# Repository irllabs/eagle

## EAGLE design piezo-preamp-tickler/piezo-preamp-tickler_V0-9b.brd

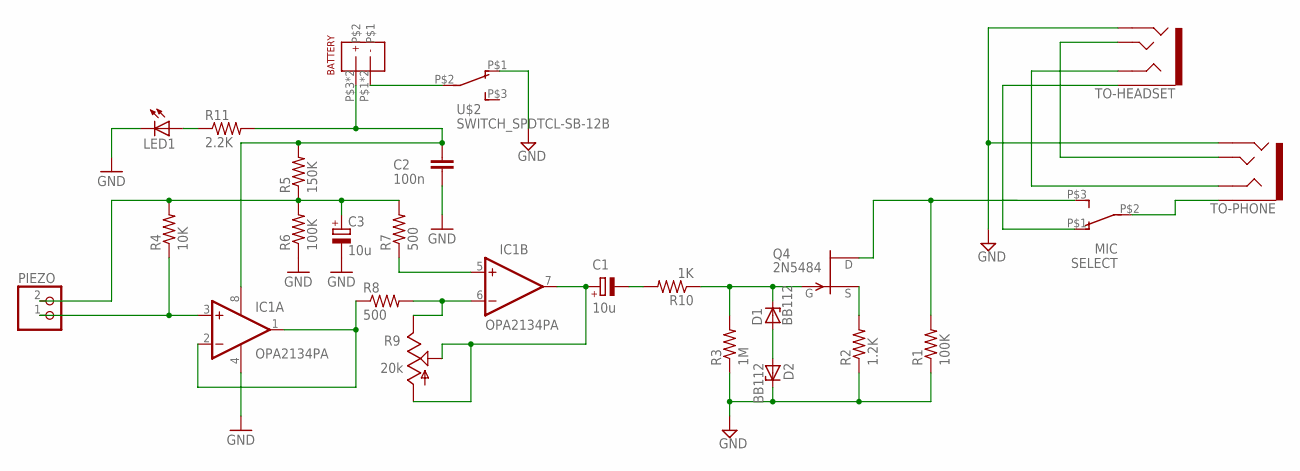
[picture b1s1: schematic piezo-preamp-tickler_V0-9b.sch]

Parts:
BATTERY: BATTERY-A27; BATTERY-A27-KEYSTONE-3651
C1, C3: 10u; TT2D5L
C2: 100n; C025-025X050
D1, D2: BB112; ZDIO-5
IC1: OPA2134PA; DIL08
LED1: LED3MM
PIEZO: JST_2PIN-THM; JST-PH-2-THM
Q4: 2N5484; TO92-
R1, R6: 100K; 0204/7
R2: 1.2K; 0204/7
R3: 1M; 0204/7
R4: 10K; 0204/7
R5: 150K; 0204/7
R7, R8: 500; 0204/7
R9: 20k; TRIMPOT-BOURNS-3306F
R10: 1K; 0204/7
R11: 2.2K; 0204/7
SELECT: MIC; SWITCH_SPDT_CL-SB-12B
TO-HEADSET: AUDIO-JACK3LGPADS; AUDIO-JACK-TRRS-SMD
TO-PHONE: AUDIO-JACK3LGPADS; AUDIO-JACK-TRRS-SMD
U$2: SWITCH_SPDTCL-SB-12B; SWITCH_SPDT_CL-SB-12B

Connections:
GND: C2.1, C3.-, D2.C, IC1.4 (V-), LED1.K (C), R1.1, R2.1, R3.1, R6.1, TO-HEADSET.RING2, TO-PHONE.RING2, U$2.P$1 (1)
unnamed: D1.A, D2.A
unnamed: BATTERY.P$1, BATTERY.P$2, U$2.P$2 (2)
unnamed: Q4.2 (S), R2.2
unnamed: IC1.5 (+IN), R7.1
unnamed: C1.+, IC1.7 (OUT), R9.P$1 (IN), R9.P$2 (WIPER)
unnamed: IC1.6 (-IN), R8.2, R9.P$3 (OUT)
unnamed: C3.+, PIEZO.2 (1), R4.2, R5.1, R6.2, R7.2
unnamed: IC1.3 (+IN), PIEZO.1 (2), R4.1
unnamed: D1.C, Q4.1 (G), R3.2, R10.1
unnamed: C1.-, R10.2
unnamed: SELECT.P$1 (1), TO-HEADSET.EARTH
unnamed: TO-HEADSET.TIP, TO-PHONE.TIP
unnamed: IC1.1 (OUT), IC1.2 (-IN), R8.1
unnamed: TO-HEADSET.RING1, TO-PHONE.RING1
unnamed: LED1.A, R11.1
unnamed: SELECT.P$2 (2), TO-PHONE.EARTH
SELECT: Q4.3 (D), R1.2, SELECT.P$3 (3)
V9V: BATTERY.P$3, BATTERY.P$4, C2.2, IC1.8 (V+), R5.2, R11.2

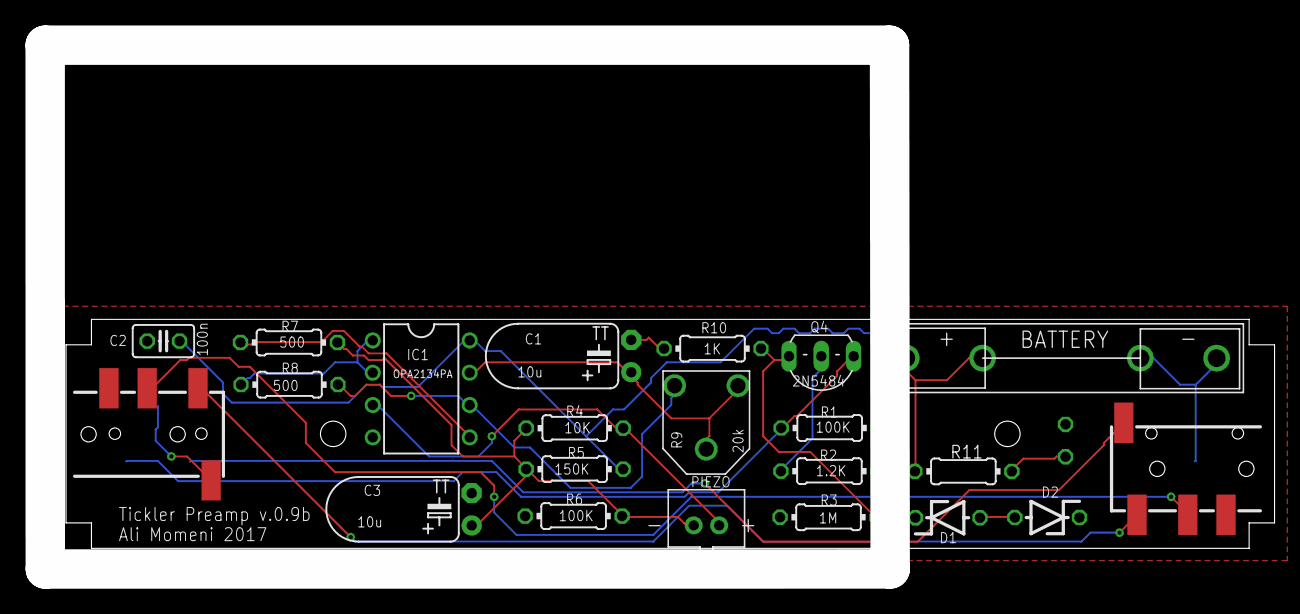
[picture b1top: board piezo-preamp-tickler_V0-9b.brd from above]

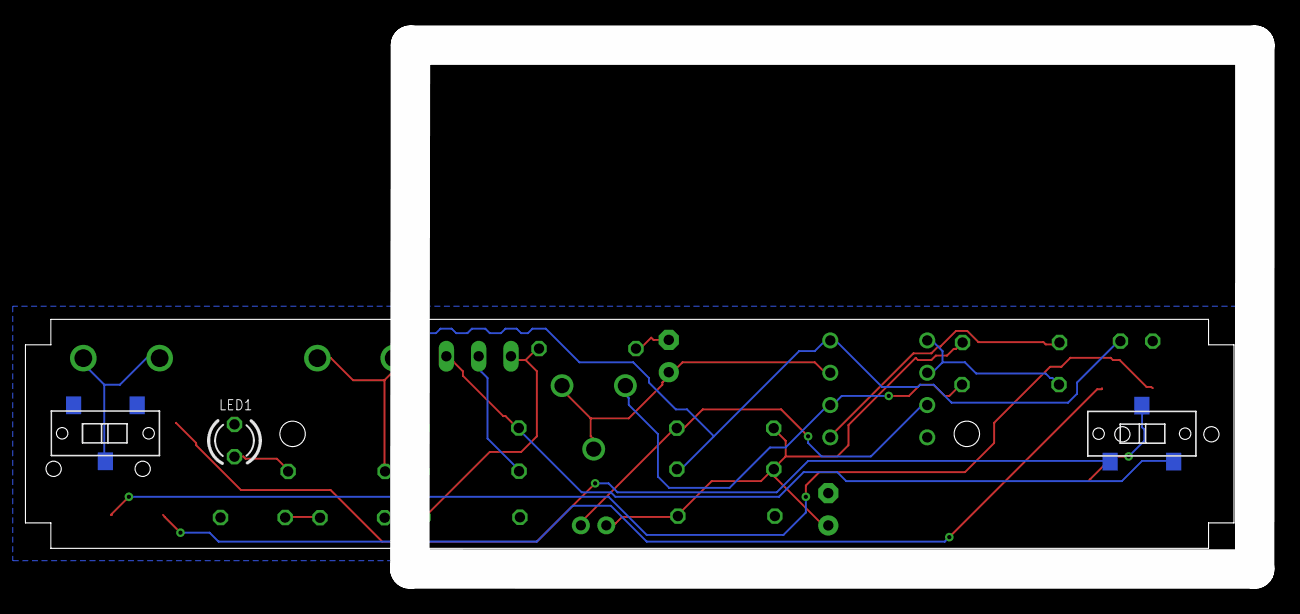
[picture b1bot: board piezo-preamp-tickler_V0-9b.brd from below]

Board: 2 copper layers, 95.1 x 41.2 mm, 25 parts (3 on the bottom side), 19 nets.

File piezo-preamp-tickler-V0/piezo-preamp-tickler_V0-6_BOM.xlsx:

Part | Value | Device | Package | Description
BAT1 |  | BATTERYA23 | BATTERY-A23 | Battery Holders
C1 | 10u | CPOL-EUE2.5-5 | E2,5-5 | POLARIZED CAPACITOR, European symbol | 732-8856-1-ND | 399-6597-ND
C2 | 100n | C-EU025-025X050 | C025-025X050 | CAPACITOR, European symbol | 445-5258-ND
C3 | 10u | CPOL-EUE2.5-5 | E2,5-5 | POLARIZED CAPACITOR, European symbol | 732-8856-1-ND | 399-6597-ND
D1 |  | 1N821 | DO35Z10 | Reference DIODE | 1N5221B - 63B
D2 |  | 1N821 | DO35Z10 | Reference DIODE | 1N5221B - 63B
IC1 | TLC272 | TLC272P | DIL08 | OP AMP | OPA2134PA-ND
IN |  | M02LOCK | 1X02_LOCK | Header 2
INPUT-SELECT |  | M03LOCK | 1X03_LOCK | Header 3
Q4 | 2N5484 | 2N5484 | TO92- | N-Channel JFETs
R1 | 10K | R-US_0204/2V | 0204V | RESISTOR, American symbol | 10.0KXBK-ND
R2 | 1.2K | R-US_0204/2V | 0204V | RESISTOR, American symbol | 1.2KADCT-ND
R3 | 1M | R-US_0204/2V | 0204V | RESISTOR, American symbol | 1.00MXBK-ND
R4 | 10K | R-US_0204/2V | 0204V | RESISTOR, American symbol | 10.0KXBK-ND
R5 | 150K | R-US_0204/2V | 0204V | RESISTOR, American symbol | 150KXBK-ND
R6 | 100K | R-US_0204/2V | 0204V | RESISTOR, American symbol | 100KXBK-ND
R7 | 1K | R-US_0204/2V | 0204V | RESISTOR, American symbol
R8 | 1K | R-US_0204/2V | 0204V | RESISTOR, American symbol
R9 |  | TRIMPOT3386 | TRIM-3386 | SMT trimmer potentiometer part number TC33X | 3352T-103LF-ND
R10 | 1K | R-US_0204/2V | 0204V | RESISTOR, American symbol
TO-HEADSET | AUDIO-JACK3 | AUDIO-JACK3 | AUDIO-JACK-TRRS-SMD | Audio jack - 3.5mm TRRS variety - two rings.
TO-PHONE | AUDIO-JACK3 | AUDIO-JACK3 | AUDIO-JACK-TRRS-SMD | Audio jack - 3.5mm TRRS variety - two rings.

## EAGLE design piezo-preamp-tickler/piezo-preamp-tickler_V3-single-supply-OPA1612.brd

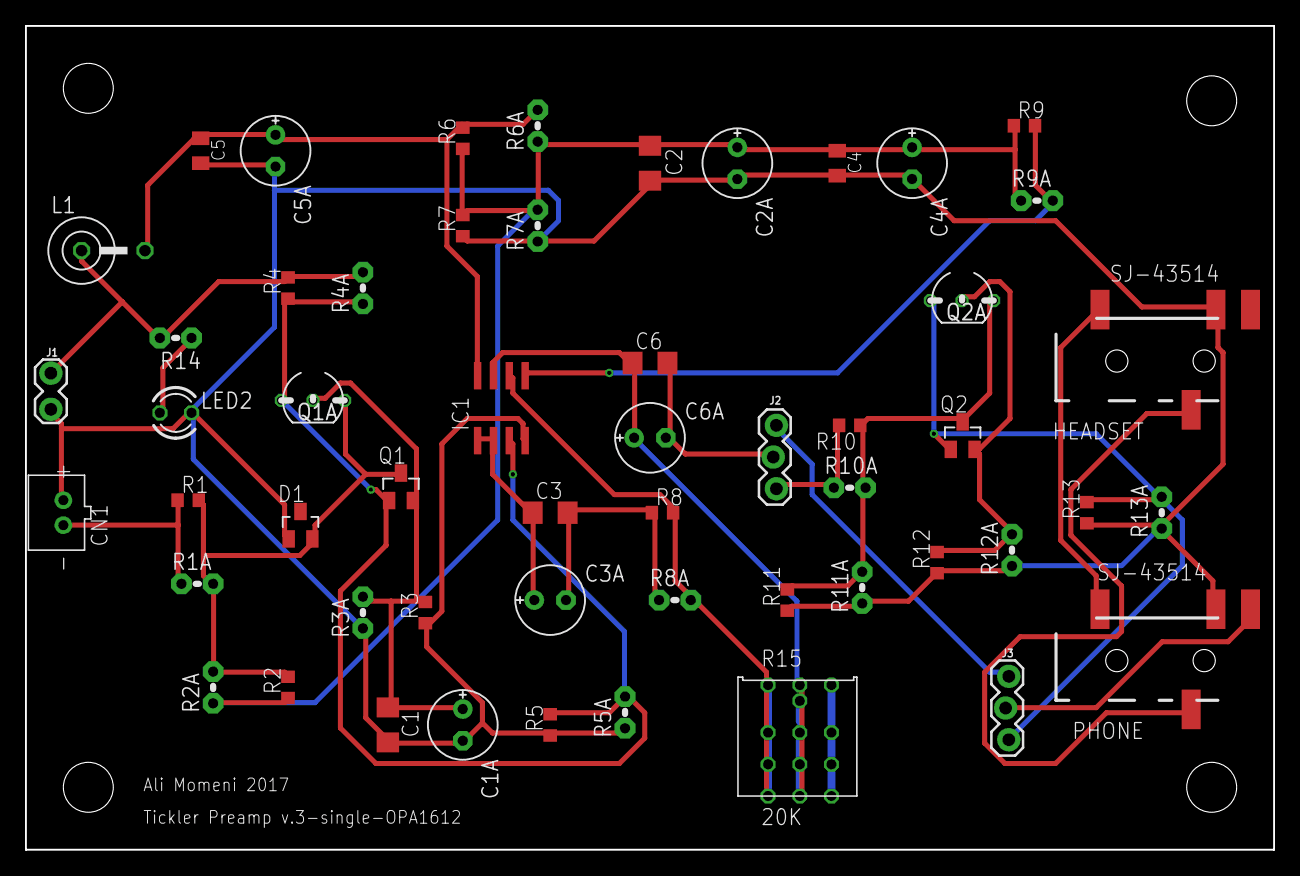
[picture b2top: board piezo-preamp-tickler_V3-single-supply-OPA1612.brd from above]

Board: 2 copper layers, 100.0 x 66.0 mm, 54 parts (0 on the bottom side), 23 nets.

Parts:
C1, C2, C6: 10uF; C1206
C1A, C2A, C4A, C6A: 10uF; E2,5-6E
C3: 100uF; C1206
C3A: 100uF; E2,5-6E
C4, C5: 0.1uF; C0805K
C5A: 0.1uF; E2,5-6E
CN1: JST-PH-2-THM
D1: BAT54S; SOT23
HEADSET: SJ-43514; TRRS_SJ-43514-SMT-TR
IC1: OPA1612; SO08
J1: 1X02_LOCK
J2, J3: phone/mixer-switch; 1X03_LOCK
L1: 100uH; LBC-SE
LED2: LED3MM
PHONE: SJ-43514; TRRS_SJ-43514-SMT-TR
Q1: J201; SOT23
Q1A, Q2A: 2N5486; TO92-
Q2: MMBFJ201; SOT23
R1, R6, R7: 100K; R0603
R1A, R6A, R7A: 100K; 0204V
R2: 10M; R0603
R2A: 10M; 0204V
R3, R12: 1.2K; R0603
R3A, R12A, R14: 1.2K; 0204V
R4, R5, R13: 2.2K; R0603
R4A, R5A, R13A: 2.2K; 0204V
R8, R9: 220; R0603
R8A, R9A: 220; 0204V
R10: 1K; R0603
R10A: 1K; 0204V
R11: 1M; R0603
R11A: 1M; 0204V
R15: 20K; TRIMPOT-MULTI

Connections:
+12V: J1.1, L1.1, R4.2, R4A.2, R14.2
DRAINE1: IC1.3, Q1.1, Q1A.3, R4.1, R4A.1, R5.2, R5A.2
GATE1: D1.2, Q1.3, Q1A.1, R1.2, R1A.2, R2.2, R2A.2
GATE2: Q2.3, Q2A.1, R10.1, R10A.2, R11.2, R11A.2
GND: C1.2, C1A.-, C2.2, C2A.-, C4.2, C4A.-, C5.2, C5A.-, CN1.1, D1.1, HEADSET.RING2, IC1.4, J1.2, LED2.K, PHONE.RING2, R3.1, R3A.1, R5.1, R5A.1, R7.1, R7A.1, R11.1, R11A.1, R12.1, R12A.1, R13.1, R13A.1
unnamed: C3.1, C3A.+, IC1.1, IC1.2
unnamed: LED2.A, R14.1
unnamed: J2.3, R10.2, R10A.1
unnamed: IC1.5, R9.2, R9A.2
unnamed: IC1.6, R8.2, R8A.2, R15.P$1, R15.P$3, R15.P$4, R15.P$6, R15.P$9
unnamed: C6.2, C6A.-, J2.2
unnamed: CN1.2, R1.1, R1A.1
unnamed: C6.1, C6A.+, IC1.7, R15.P$10, R15.P$12, R15.P$13, R15.P$15, R15.P$16, R15.P$18
unnamed: C5.1, C5A.+, IC1.8, L1.2, R6.2, R6A.2
unnamed: C2.1, C2A.+, C4.1, C4A.+, R2.1, R2A.1, R6.1, R6A.1, R7.2, R7A.2, R9.1, R9A.1
unnamed: J2.1, J3.1
unnamed: HEADSET.TIP, PHONE.TIP
unnamed: HEADSET.RING1, PHONE.RING1
unnamed: J3.2, PHONE.EARTH
unnamed: C3.2, C3A.-, R8.1, R8A.1
NAME: J3.3, Q2.1, Q2A.3, R13.2, R13A.2
SOURCE: Q2.2, Q2A.2, R12.2, R12A.2
SOURCE1: C1.1, C1A.+, Q1.2, Q1A.2, R3.2, R3A.2

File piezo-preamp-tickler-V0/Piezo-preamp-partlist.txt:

Partlist

Exported from piezo-preamp-tickler_V3-2_single-supply-OPA1642.sch at 12/20/2017 9:03 PM

"EAGLE Version 8.5.1 Copyright (c) 1988-2017 Autodesk, Inc."

Assembly variant: 

Part       Value          Device                    Package               Library             Sheet

C2         10uF           C-USC1206                 C1206                 rcl                 1
C3         100uF          CAP_TANTALUMD/7343_REFLOW EIA7343-31/D-R        microbuilder        1
C4         0.1uF          C-USC0805K                C0805K                adafruit            1
C5         0.1uF          C-USC0805K                C0805K                adafruit            1
C6         10uF           C-USC1206                 C1206                 adafruit            1
CN1                       JST_2PIN-THM              JST-PH-2-THM          adafruit            1
D1         1N4148W        ZENER-DIOD                SOD123                CMU-ArtFab          1
D2         1N4148W        ZENER-DIOD                SOD123                CMU-ArtFab          1
HEADSET    SJ-43514       TRRS-3.5MMLGPADS          TRRS_SJ-43514-SMT-TR  CMU-ArtFab          1
IC1        OPA1612        OPA2134UA                 SO08                  linear              1
J1                        CONN_02LOCK               1X02_LOCK             SparkFun-Connectors 1
L1         100uH          L-USL3225P                L3225P                rcl                 1
LED1                      LED3MM                    LED3MM                led                 1
"MIXER-OUT  TRS-1/8""-3.5MM TRS-1/8""-3.5MM            TRS_SJ-3524-SMT       CMU-ArtFab          1"
PHONE      SJ-43514       TRRS-3.5MMLGPADS          TRRS_SJ-43514-SMT-TR  CMU-ArtFab          1
Q2         MMBFJ201       SST5484                   SOT23                 transistor-fet      1
R1         100K           R-US_R0603                R0603                 CMU-ArtFab          1
R2         10M            R-US_R0603                R0603                 CMU-ArtFab          1
R6         100K           R-US_R0603                R0603                 CMU-ArtFab          1
R7         100K           R-US_R0603                R0603                 CMU-ArtFab          1
R8         220            R-US_R0603                R0603                 CMU-ArtFab          1
R9         220            R-US_R0603                R0603                 CMU-ArtFab          1
R10        1K             R-US_R0603                R0603                 CMU-ArtFab          1
R11        1M             R-US_R0603                R0603                 CMU-ArtFab          1
R12        1.2K           R-US_R0603                R0603                 CMU-ArtFab          1
R13        2.2K           R-US_R0603                R0603                 CMU-ArtFab          1
R14        1.2K           R-US_R0603                R0603                 CMU-ArtFab          1
R15        20K            POTTRIMPOT-MULTI          TRIMPOT-MULTI         CMU-ArtFab          1
SW1-INPUT  SPDTCSS-1210B  SWITCH_SPDTCSS-1210B      SWITCH_SPDT_CSS-1210B CMU-ArtFab          1
SW1-OUTPUT SWITCH_DPDT    SWITCH_DPDT               SWITCH_DPDT_CL-SB-22B CMU-ArtFab          1

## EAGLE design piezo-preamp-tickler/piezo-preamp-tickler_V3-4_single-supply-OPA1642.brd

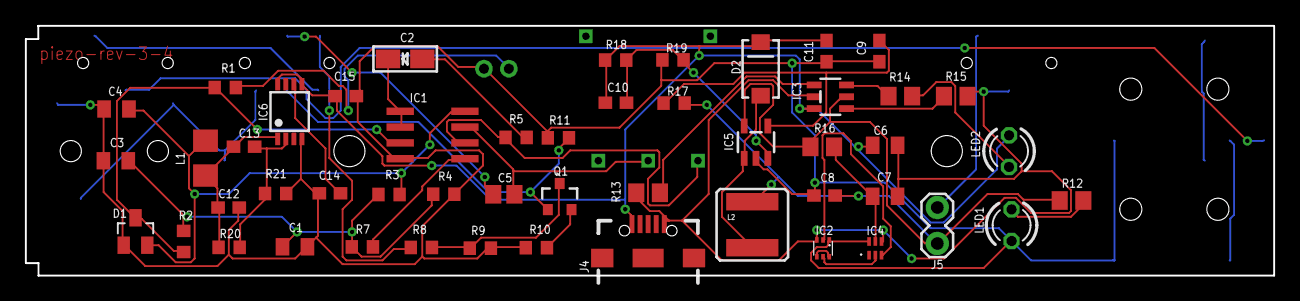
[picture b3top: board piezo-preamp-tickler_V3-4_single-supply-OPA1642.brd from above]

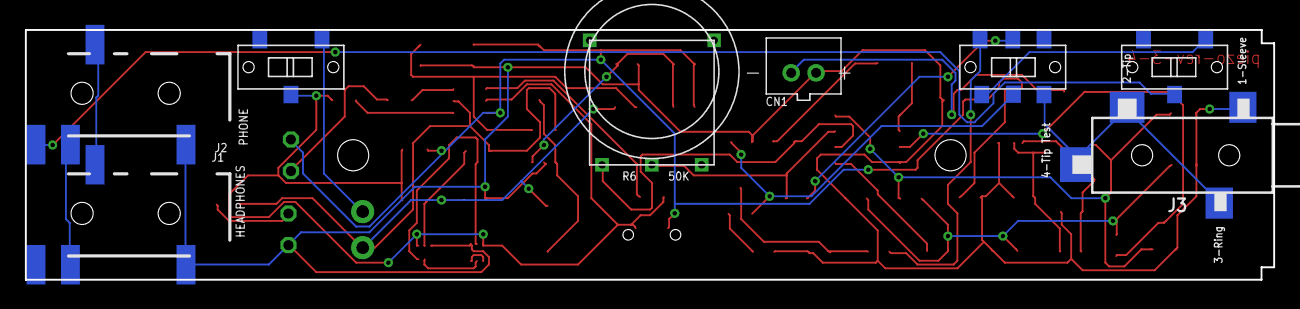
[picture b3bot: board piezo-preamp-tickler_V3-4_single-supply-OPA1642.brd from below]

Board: 2 copper layers, 100.3 x 20.1 mm, 58 parts (8 on the bottom side), 39 nets.

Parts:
C1, C6: 10uF; C0805K
C2: 100uF; EIA3216-18/A-R
C3, C4, C7: 0.1uF; C0805K
C5: 10uF; C0805
C8, C12, C15: 10uF; C0603
C9: 56nf; C0603
C10: 2.2pf; C0603
C11: 68uF; C0603
C13, C14: 10nF; C0603
CN1: JST-PH-2-THM
D1: BAT54S; SOT23
D2: 10BQ015; SMA-DIODE
IC1: OPA1642; SO08
IC2: DMN2400; SOT-563
IC3: BQ21040; SOT23-6
IC4: BQ297X; WSON-6
IC5: SC4503; SOT23-5
IC6: TPS7A49; MSOP-8
J1: HEADPHONES; TRRS_SJ-43514-SMT-TR
J2: PHONE; TRRS_SJ-43514-SMT-TR
J3: Mixer; TRS_SJ-3524-SMT
J4: USB-B-MICRO-SMD_RED_PASTE
J5: Battery; 1X02_LOCK
L1: 100uH; L3225P
L2: 2.7uH; CR54
LED1: Power; LED3MM
LED2: Charge; LED3MM
Q1: MMBFJ201; SOT23-3
R1, R3, R4: 100K; R0603
R2: 10M; R0603
R5, R7: 220; R0603
R6: 50K; POT-THUMB-14MM_ALPHA-RV100F-30-4K1B-B10K-B301
R8: 1K; R0603
R9, R18: 1M; R0603
R10: 1.2K; R0603
R11: 2.2K; R0603
R12: 390; R0805
R13, R15: 10k; R0805
R14: 1k; R0805
R16: 330; R0805
R17: 15k; R0603
R19, R21: 100k; R0603
R20: 91.2k; R0603
SW1: SWITCH_DPDT; SWITCH_DPDT_CL-SB-22B
SW2: INPUT-select; SWITCH_SPDT_CL-SB-12B
SW3: SPDT; SWITCH_SPDT_CL-SB-12B

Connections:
+12V: C12.1, C13.1, IC6.1, L1.1, R20.1
GND: C1.2, C3.2, C4.2, C8.2, C9.2, C11.2, C12.2, C14.2, C15.2, CN1.1, D1.1, IC1.4, IC2.1, IC4.6, IC5.2, IC6.4, J1.TIP, J2.TIP, J3.1, LED1.K, R4.1, R9.1, R10.1, R11.1, R19.1, R21.2
GND2: C6.2, C7.2, IC2.3, IC3.5, IC4.4, J4.GND, R13.1, R15.1, SW3.P$2
unnamed: CN1.2, R1.1
unnamed: Q1.2, R10.2
unnamed: IC1.5, R7.1
unnamed: C5.1, IC1.7, R6.P$2
unnamed: IC1.6, R5.2, R6.P$1
unnamed: D1.3, IC1.3, R1.2, R2.2
unnamed: Q1.3, R8.1, R9.2
unnamed: R8.2, SW1.4
unnamed: J3.2, J3.3, J3.4, SW1.3
unnamed: J1.RING1, J2.RING1
unnamed: C2.-, R5.1
unnamed: J1.RING2, J2.RING2
unnamed: C5.2, SW1.5
unnamed: J2.EARTH, SW2.P$2
unnamed: LED1.A, R12.1
unnamed: SW1.1, SW2.P$1
unnamed: J5.2, SW3.P$1
unnamed: LED2.K, R14.1
unnamed: C1.1, C3.1, R2.1, R3.1, R4.2, R7.2
unnamed: C2.+, IC1.1, IC1.2
unnamed: C4.1, D1.2, IC1.8, L1.2, R3.2
unnamed: C13.2, IC6.2, R20.2, R21.1
unnamed: IC3.3, R14.2
unnamed: C14.1, IC6.6
unnamed: C9.1, IC5.4, R17.1
unnamed: C10.2, IC5.3, R18.1, R19.2
unnamed: IC3.1, R15.2
unnamed: D2.A, IC5.1, L2.P$2
unnamed: IC3.4, R13.2
unnamed: C7.1, IC4.5, R16.2
unnamed: IC2.4, IC2.6
unnamed: IC2.5, IC4.2
unnamed: IC2.2, IC4.3
SELECT: Q1.1, R11.2, SW1.2
V+: C6.1, C10.1, C11.1, C15.1, D2.C, IC3.6, IC6.5, IC6.8, J4.VBUS, LED2.A, R18.2
VBAT: C8.1, IC3.2, IC5.5, J5.1, L2.P$1, R12.2, R16.1, R17.2

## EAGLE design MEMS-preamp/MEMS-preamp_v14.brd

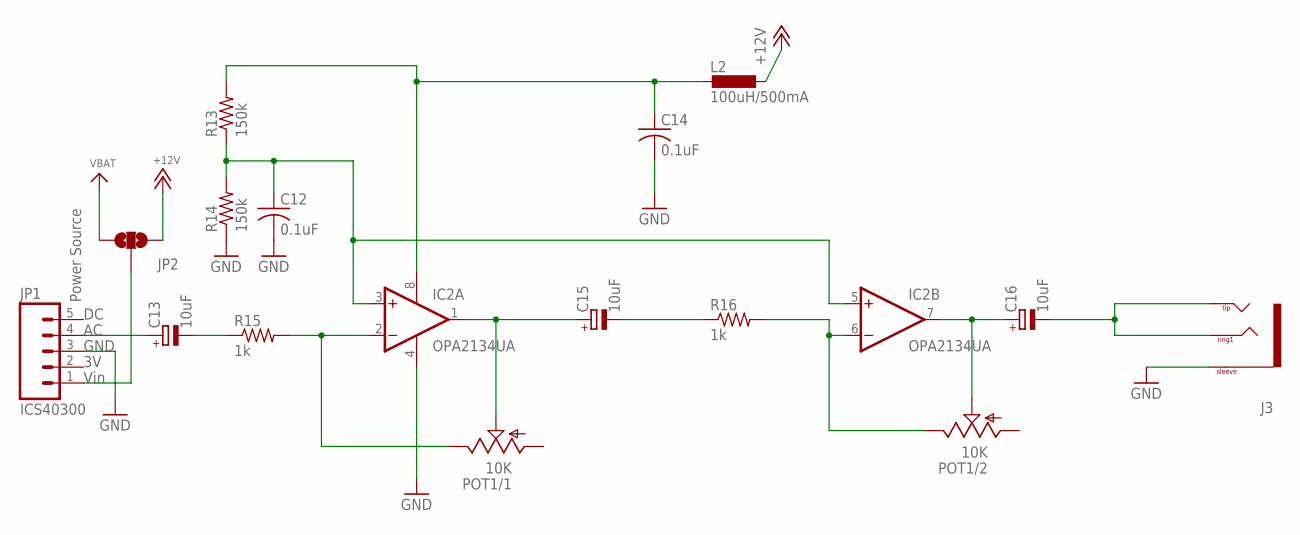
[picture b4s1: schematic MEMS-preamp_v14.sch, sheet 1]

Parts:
C12: 0.1uF; C0805
C13, C15, C16: 10uF; PANASONIC_B
C14: 0.1uF; C0805K
IC2: OPA2134UA; SO08
J3: TRS-1/8"-3.5MM; TRS_SJ-3524-SMT
JP1: ICS40300; 1X05_SMD_STRAIGHT
JP2: Power Source; SMT-JUMPER_3_NO_SILK
L2: 100uH/500mA; L3225M
POT1: 10K; PTV112
R13, R14: 150k; R0603
R15, R16: 1k; R0603

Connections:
+12V: JP2.3, L2.1; also elsewhere on the board
GND: C12.2, C14.2, IC2.4 (V-), J3.1 (SLEEVE), JP1.3, R14.1; also elsewhere on the board
unnamed: C13.+, JP1.4
unnamed: C15.-, R16.1
unnamed: IC2.2 (-IN), POT1.1.3 (E), R15.2
unnamed: C16.-, J3.2 (TIP), J3.3 (RING1), J3.4 (TIP)
unnamed: C12.1, IC2.3 (+IN), IC2.5 (+IN), R13.1, R14.2
unnamed: C15.+, IC2.1 (OUT), POT1.1.2 (S)
unnamed: C16.+, IC2.7 (OUT), POT1.2.2 (S)
unnamed: C14.1, IC2.8 (V+), L2.2, R13.2
unnamed: IC2.6 (-IN), POT1.2.3 (E), R16.2
unnamed: C13.-, R15.1
VBAT: JP2.1; also elsewhere on the board
VIN: JP1.1, JP2.2

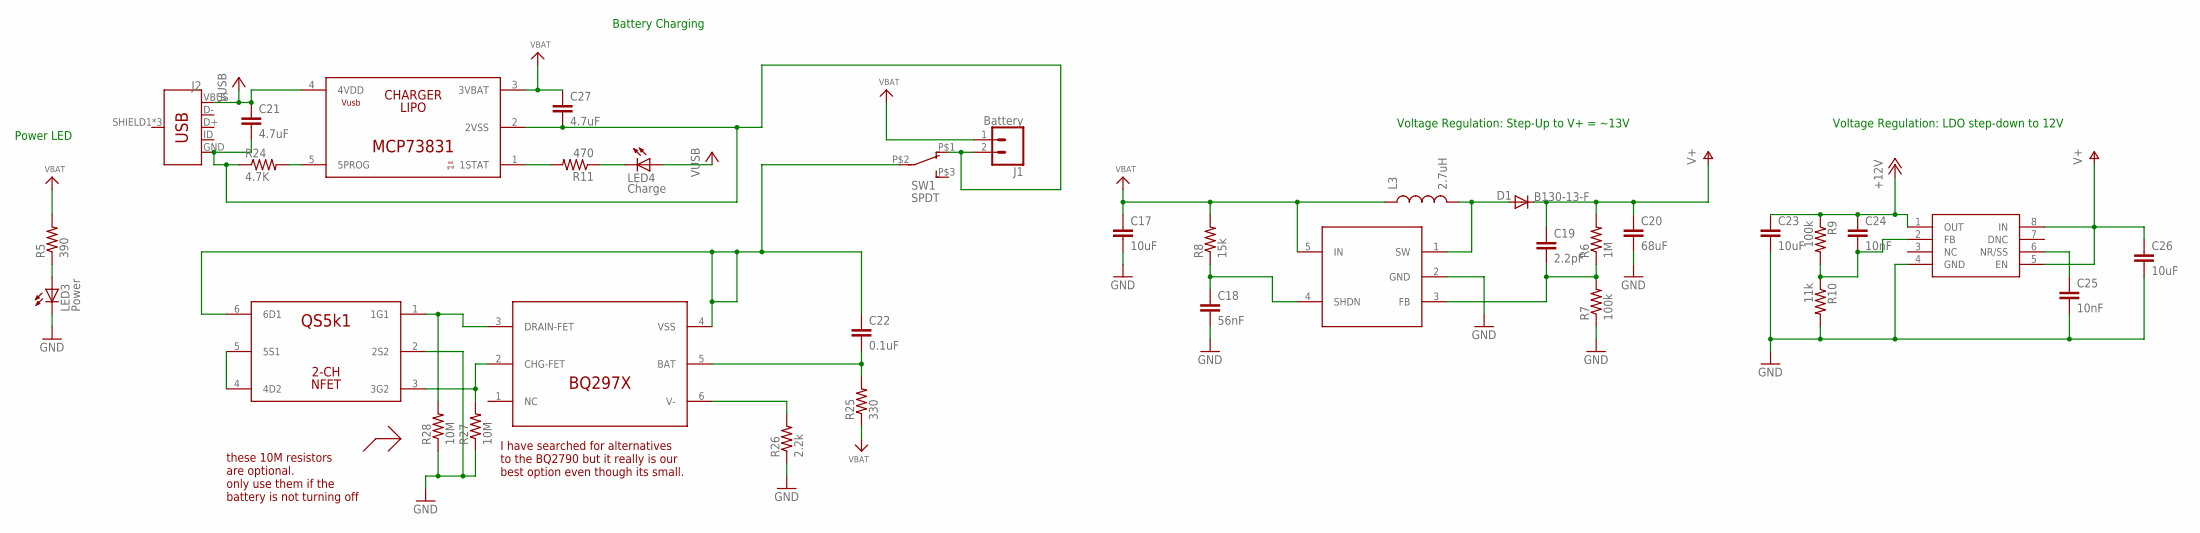
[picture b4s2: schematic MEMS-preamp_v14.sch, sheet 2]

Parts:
C17, C23, C26: 10uF; C0603
C18: 56nF; C0603
C19: 2.2pF; C0603
C20: 68uF; C1206
C21, C27: 4.7uF; C0603
C22: 0.1uF; C0603
C24, C25: 10nF; C0603
D1: B130-13-F; SMA-DIODE
IC7: TPS7A49; MSOP-8
IC8: BQ297X; WSON-6-LONG
IC9: SC4503; SOT23-5
IC10: MCP73831; SOT-23-5
IC11: QS6K1; SOT457R_PHILIPS
J1: Battery; 1X02_LOCK
J2: USB_MICRO-BREDUCED_PASTE; USB-B-MICRO-SMD_RED_PASTE
L3: 2.7uH; CR54
LED3: Power; LED3MM
LED4: Charge; LED3MM
R5: 390; R0603
R6: 1M; R0603
R7, R9: 100k; R0603
R8: 15k; R0603
R10: 11k; R0603
R11: 470; R0603
R24: 4.7K; R0603
R25: 330; R0603
R26: 2.2k; R0603
R27, R28: 10M; R0603
SW1: SPDT; SWITCH_SPDT_CL-SB-12B

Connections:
+5V: C21.1, IC10.4 (4VDD), J2.VBUS, LED4.A
+12V: C23.1, C24.1, IC7.1 (OUT), R9.1; also elsewhere on the board
BATGND1: C22.1, IC8.4 (VSS), IC11.6 (6D1), SW1.P$2 (2)
GND: C17.2, C18.2, C20.2, C23.2, C25.2, C26.2, IC7.4 (GND), IC9.2 (GND), IC11.2 (2S2), LED3.K (C), R7.1, R10.2, R26.1, R27.1, R28.1; also elsewhere on the board
unnamed: LED3.A, R5.1
unnamed: D1.A, IC9.1 (SW), L3.P$2 (2)
unnamed: C18.1, IC9.4 (SHDN), R8.1
unnamed: C19.2, IC9.3 (FB), R6.1, R7.2
unnamed: C24.2, IC7.2 (FB), R9.2, R10.1
unnamed: C25.1, IC7.6 (NR/SS)
unnamed: LED4.K (C), R11.1
unnamed: C22.2, IC8.5 (BAT), R25.2
unnamed: IC10.5 (5PROG), R24.2
unnamed: IC10.1 (1STAT), R11.2
unnamed: IC11.4 (4D2), IC11.5 (5S1)
unnamed: IC8.3 (DRAIN-FET), IC11.1 (1G1), R28.2
unnamed: IC8.2 (CHG-FET), IC11.3 (3G2), R27.2
unnamed: IC8.6 (V-), R26.2
USBGND1: C21.2, C27.2, IC10.2 (2VSS), J1.2, J2.GND, R24.1, SW1.P$1 (1)
V+: C19.1, C20.1, C26.1, D1.C, IC7.5 (EN), IC7.8 (IN), R6.2
VBAT: C17.1, C27.1, IC9.5 (IN), IC10.3 (3VBAT), J1.1, L3.P$1 (1), R5.2, R8.2, R25.1; also elsewhere on the board

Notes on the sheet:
Voltage Regulation: Step-Up to V+ = ~13V
Power LED
Voltage Regulation: LDO step-down to 12V
Battery Charging
I have searched for alternatives to the BQ2790 but it really is our best option even though its small.
these 10M resistors are optional. only use them if the battery is not turning off

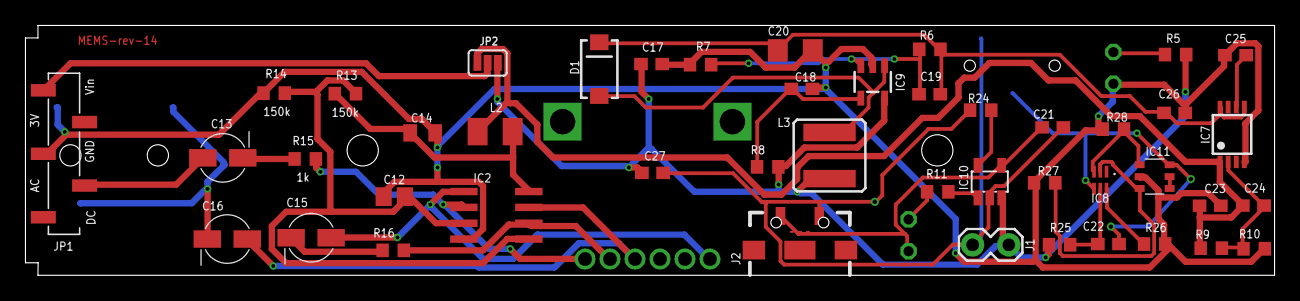
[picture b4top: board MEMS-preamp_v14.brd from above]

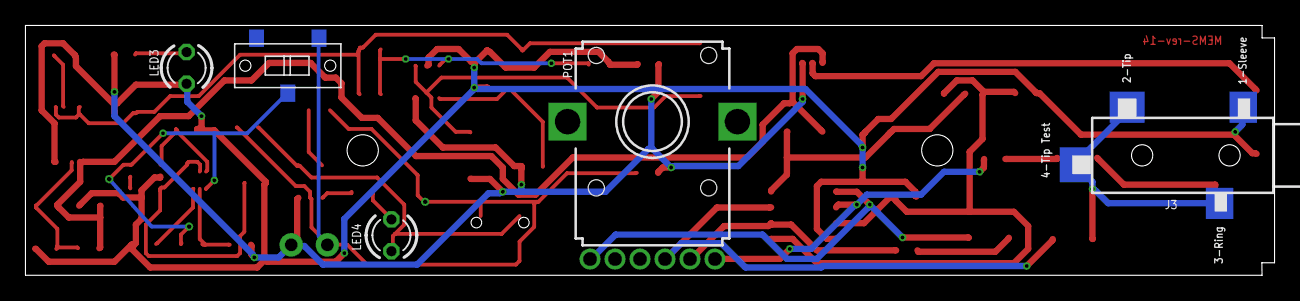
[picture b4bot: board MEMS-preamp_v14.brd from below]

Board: 2 copper layers, 100.0 x 20.0 mm, 50 parts (5 on the bottom side), 32 nets.

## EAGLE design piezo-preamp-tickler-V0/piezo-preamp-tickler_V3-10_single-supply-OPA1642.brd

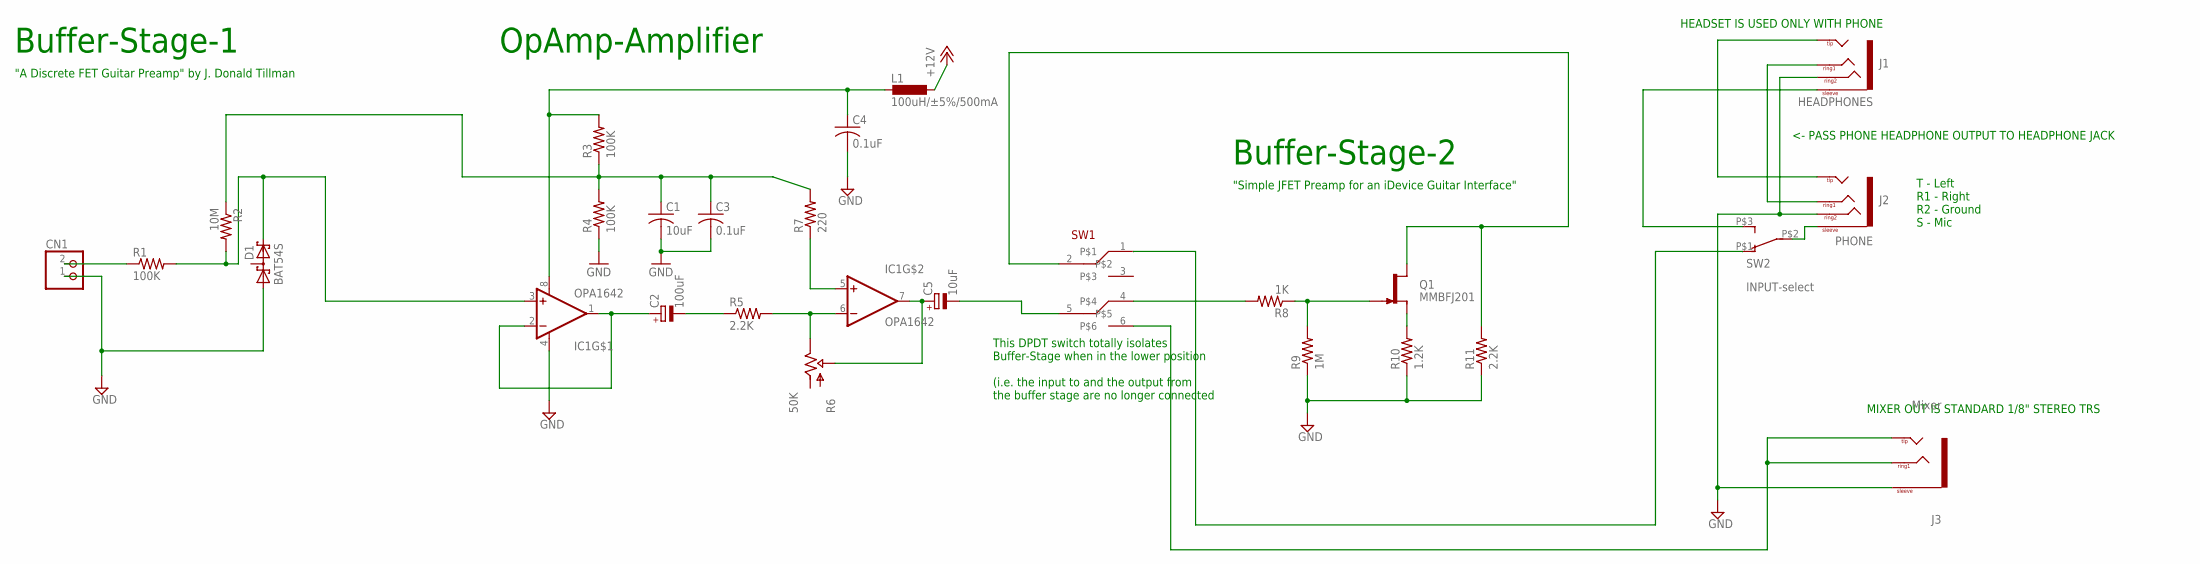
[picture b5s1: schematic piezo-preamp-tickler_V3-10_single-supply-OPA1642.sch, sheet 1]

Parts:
C1: 10uF; C0805K
C2: 100uF; PANASONIC_C
C3, C4: 0.1uF; C0805K
C5: 10uF; PANASONIC_B
CN1: JST_2PIN-THM; JST-PH-2-THM
D1: BAT54S; SOT23
IC1: OPA1642; SO08
J1: HEADPHONES; TRRS_SJ-43514-SMT-TR
J2: PHONE; TRRS_SJ-43514-SMT-TR
J3: Mixer; TRS_SJ-3524-SMT
L1: 100uH/±5%/500mA; L3225M
Q1: MMBFJ201; SOT23-3
R1, R3, R4: 100K; R0603
R2: 10M; R0603
R5, R11: 2.2K; R0603
R6: 50K; THUMBPOT14MM
R7: 220; R0603
R8: 1K; R0603
R9: 1M; R0603
R10: 1.2K; R0603
SW1: SWITCH_DPDT; SWITCH_DPDT_CL-SB-22B
SW2: INPUT-select; SWITCH_SPDT_CL-SB-12B

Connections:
+12V: L1.1; also elsewhere on the board
GND: C1.2, C3.2, C4.2, CN1.1 (2), D1.1 (A1), IC1.4 (V-), J1.RING2, J2.RING2, J3.1 (SLEEVE), R4.1, R9.1, R10.1, R11.1; also elsewhere on the board
unnamed: D1.2 (C2), IC1.3 (+IN), R1.2, R2.2
unnamed: CN1.2 (1), R1.1
unnamed: Q1.2 (S), R10.2
unnamed: J1.EARTH (SLEEVE), SW2.P$3 (3)
unnamed: IC1.5 (+IN), R7.1
unnamed: C5.+, IC1.7 (OUT), R6.P$2 (WIPER)
unnamed: IC1.6 (-IN), R5.2, R6.P$3 (OUT)
unnamed: C4.1, IC1.8 (V+), L1.2, R3.2
unnamed: C1.1, C3.1, R2.1, R3.1, R4.2, R7.2
unnamed: Q1.3 (G), R8.1, R9.2
unnamed: R8.2, SW1.4
unnamed: J3.2 (TIP), J3.3 (RING1), J3.4 (TIP), SW1.6
unnamed: J1.RING1, J2.RING1
unnamed: C2.-, R5.1
unnamed: C5.-, SW1.5
unnamed: J2.EARTH (SLEEVE), SW2.P$2 (2)
unnamed: SW1.1, SW2.P$1 (1)
unnamed: C2.+, IC1.1 (OUT), IC1.2 (-IN)
unnamed: J1.TIP, J2.TIP
SELECT: Q1.1 (D), R11.2, SW1.2

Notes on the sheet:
Buffer-Stage-1
OpAmp-Amplifier
Buffer-Stage-2
"A Discrete FET Guitar Preamp" by J. Donald Tillman
"Simple JFET Preamp for an iDevice Guitar Interface"
T - Left R1 - Right R2 - Ground S - Mic
HEADSET IS USED ONLY WITH PHONE
MIXER OUT IS STANDARD 1/8" STEREO TRS
<- PASS PHONE HEADPHONE OUTPUT TO HEADPHONE JACK
This DPDT switch totally isolates Buffer-Stage when in the lower position (i.e. the input to and the output from the buffer stage are no longer connected

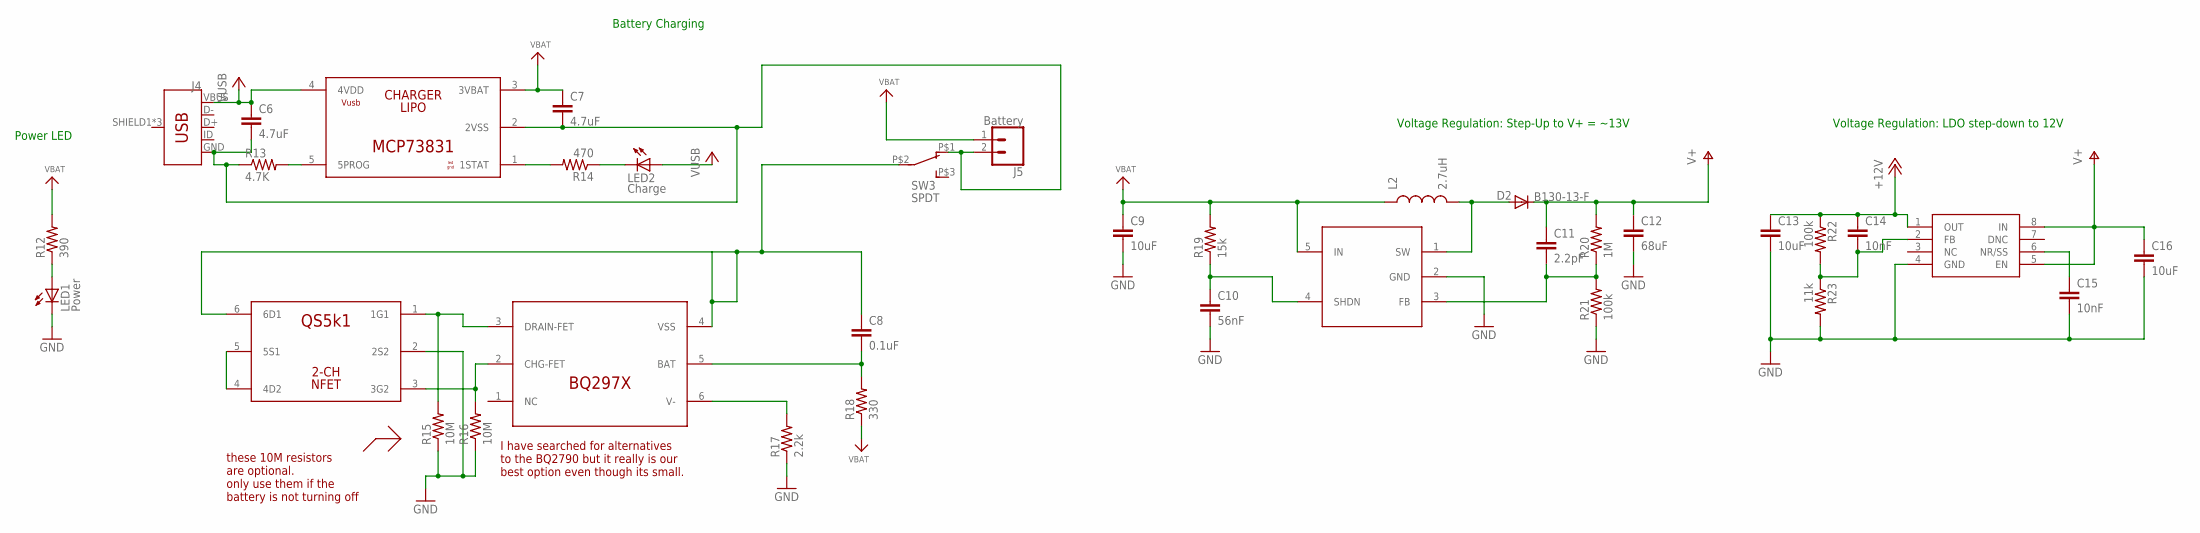
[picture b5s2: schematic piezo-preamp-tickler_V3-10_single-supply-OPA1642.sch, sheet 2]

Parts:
C6, C7: 4.7uF; C0603
C8: 0.1uF; C0603
C9, C13, C16: 10uF; C0603
C10: 56nF; C0603
C11: 2.2pF; C0603
C12: 68uF; C1206
C14, C15: 10nF; C0603
D2: B130-13-F; SMA-DIODE
IC2: MCP73831; SOT-23-5
IC3: QS6K1; SOT457R_PHILIPS
IC4: BQ297X; WSON-6-LONG
IC5: SC4503; SOT23-5
IC6: TPS7A49; MSOP-8
J4: USB_MICRO-BREDUCED_PASTE; USB-B-MICRO-SMD_RED_PASTE
J5: Battery; 1X02_LOCK
L2: 2.7uH; CR54
LED1: Power; LED3MM
LED2: Charge; LED3MM
R12: 390; R0603
R13: 4.7K; R0603
R14: 470; R0603
R15, R16: 10M; R0603
R17: 2.2k; R0603
R18: 330; R0603
R19: 15k; R0603
R20: 1M; R0603
R21, R22: 100k; R0603
R23: 11k; R0603
SW3: SPDT; SWITCH_SPDT_CL-SB-12B

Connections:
+5V: C6.1, IC2.4 (4VDD), J4.VBUS, LED2.A
+12V: C13.1, C14.1, IC6.1 (OUT), R22.1; also elsewhere on the board
BATGND: C8.1, IC3.6 (6D1), IC4.4 (VSS), SW3.P$2 (2)
GND: C9.2, C10.2, C12.2, C13.2, C15.2, C16.2, IC3.2 (2S2), IC5.2 (GND), IC6.4 (GND), LED1.K (C), R15.1, R16.1, R17.1, R21.1, R23.2; also elsewhere on the board
unnamed: LED1.A, R12.1
unnamed: IC2.5 (5PROG), R13.2
unnamed: LED2.K (C), R14.1
unnamed: IC3.4 (4D2), IC3.5 (5S1)
unnamed: IC2.1 (1STAT), R14.2
unnamed: C14.2, IC6.2 (FB), R22.2, R23.1
unnamed: IC3.1 (1G1), IC4.3 (DRAIN-FET), R15.2
unnamed: C15.1, IC6.6 (NR/SS)
unnamed: C10.1, IC5.4 (SHDN), R19.1
unnamed: C11.2, IC5.3 (FB), R20.1, R21.2
unnamed: IC3.3 (3G2), IC4.2 (CHG-FET), R16.2
unnamed: D2.A, IC5.1 (SW), L2.P$2 (2)
unnamed: IC4.6 (V-), R17.2
unnamed: C8.2, IC4.5 (BAT), R18.2
USBGND: C6.2, C7.2, IC2.2 (2VSS), J4.GND, J5.2, R13.1, SW3.P$1 (1)
V+: C11.1, C12.1, C16.1, D2.C, IC6.5 (EN), IC6.8 (IN), R20.2
VBAT: C7.1, C9.1, IC2.3 (3VBAT), IC5.5 (IN), J5.1, L2.P$1 (1), R12.2, R18.1, R19.2

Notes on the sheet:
Voltage Regulation: Step-Up to V+ = ~13V
Power LED
Voltage Regulation: LDO step-down to 12V
Battery Charging
I have searched for alternatives to the BQ2790 but it really is our best option even though its small.
these 10M resistors are optional. only use them if the battery is not turning off

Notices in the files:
parts and their libraries:
SparkFun-Connectors: Licensing: Creative Commons ShareAlike 4.0 International - https://creativecommons.org/licenses/by-sa/4.0
microbuilder: This work is placed in the public domain, and may be freely used for commercial and non-commercial work with the following conditions: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
